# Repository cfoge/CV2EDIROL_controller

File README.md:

# CV2EDIROL_controller
An open-source CV to MIDI controller for EDIROL V4 and V8 video mixers

Programing guide: [link](https://docs.google.com/document/d/18BVAYo14xsvCTc38q8JL8ZcNEWuq-BcZkRPL7WG5LXM/edit?usp=sharing)

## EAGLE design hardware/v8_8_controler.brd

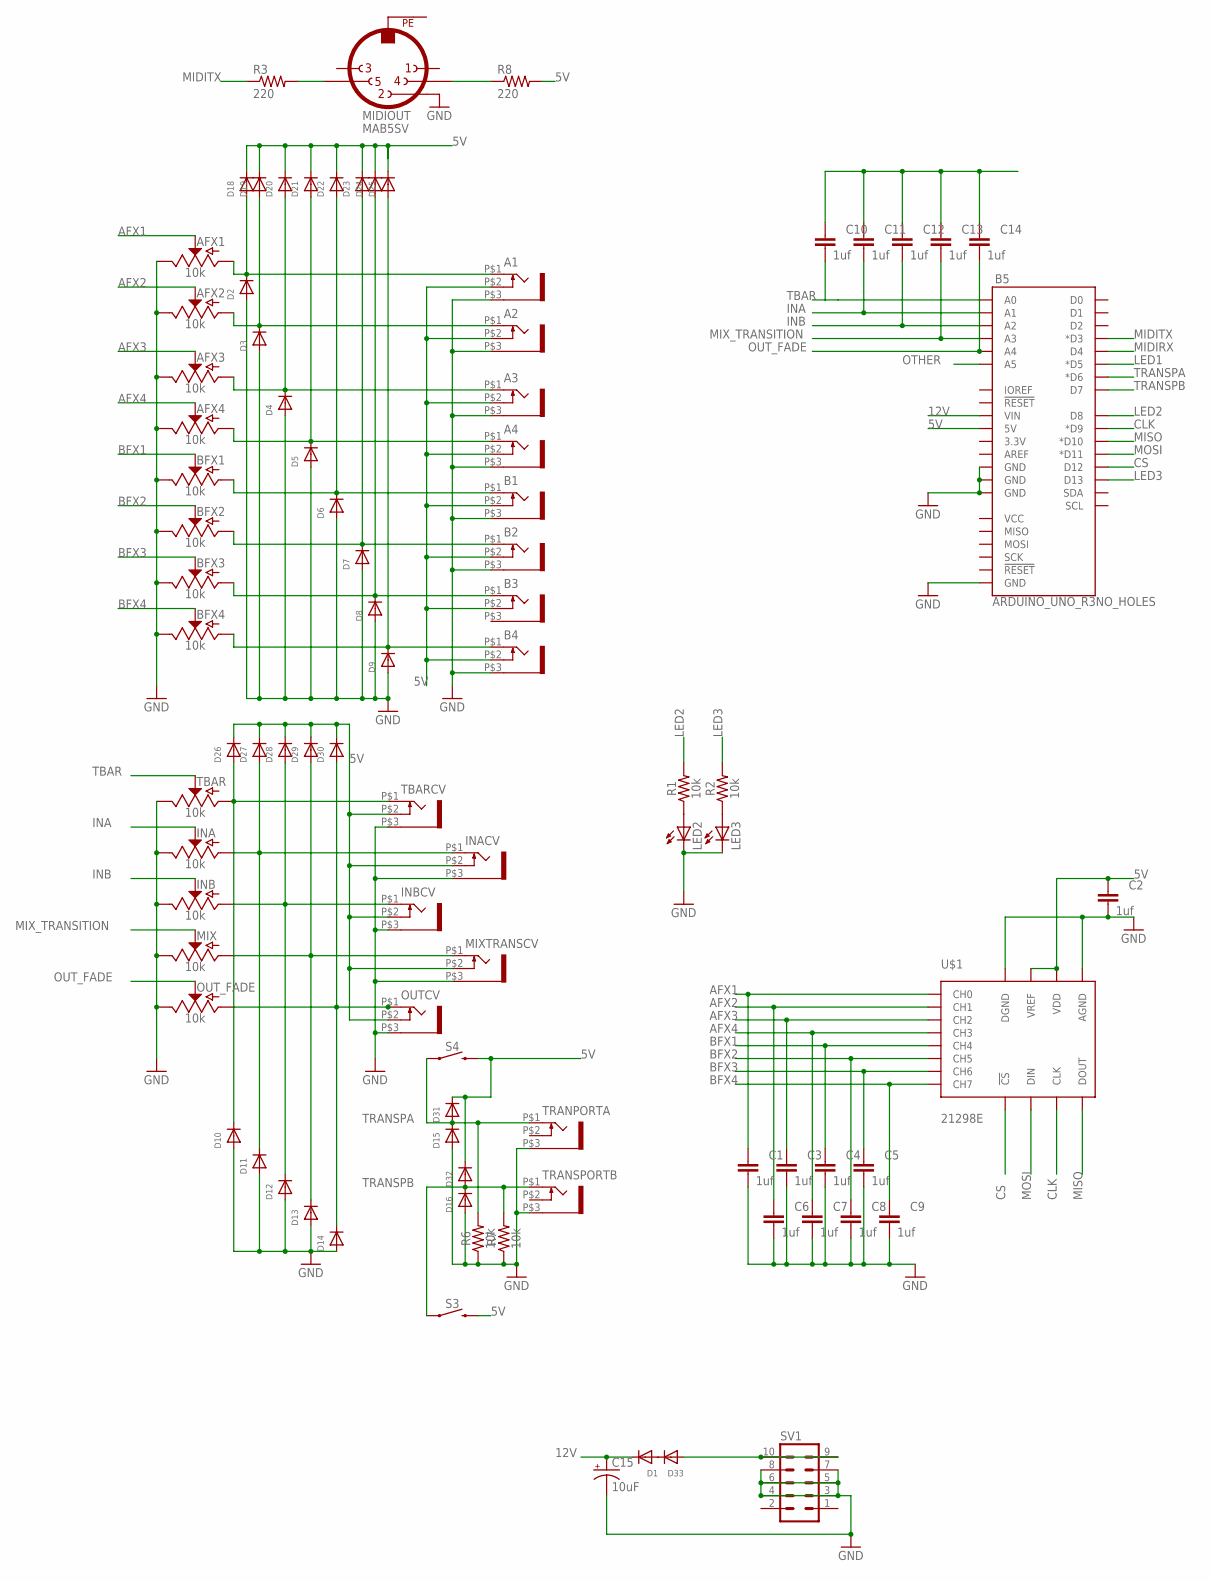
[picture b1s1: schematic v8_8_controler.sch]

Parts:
A1, A2, A3, A4: WQP-PJ301M-12_JACK
AFX1, AFX2, AFX3, AFX4: 10k; POT-PTH-ALPS
B1, B2, B3, B4: WQP-PJ301M-12_JACK
B5: ARDUINO_UNO_R3NO_HOLES; ARDUINO_R3_NO_HOLES
BFX1, BFX2, BFX3, BFX4: 10k; POT-PTH-ALPS
C1, C2, C3, C4, C5, C6, C7, C8, C9, C10, C11, C12, C13, C14: 1uf; 0805
C15: 10uF; EIA3528
D1, D2, D3, D4, D5, D6, D7, D8, D9, D10, D11, D12, D13, D14, D15, D16, D18, D19, D20, D21, D22, D23, D24, D25, D26, D27, D28, D29, D30, D31, D32, D33: DIODE_SOD-123FL; SOD-123FL
INA: 10k; POT-PTH-ALPS
INACV: WQP-PJ301M-12_JACK
INB: 10k; POT-PTH-ALPS
INBCV: WQP-PJ301M-12_JACK
LED2, LED3: LED3MM
MIDIOUT: MAB5SV
MIX: 10k; POT-PTH-ALPS
MIXTRANSCV: WQP-PJ301M-12_JACK
OUTCV: WQP-PJ301M-12_JACK
OUT_FADE: 10k; POT-PTH-ALPS
R1, R2, R6, R7: 10k; 0805
R3, R8: 220; R0805
S3, S4: MOMENTARY-SWITCH-SPST-PTH-6.0MM; TACTILE_SWITCH_PTH_6.0MM
SV1: MA05-2
TBAR: 10k; POT-PTH-ALPS
TBARCV: WQP-PJ301M-12_JACK
TRANPORTA: WQP-PJ301M-12_JACK
TRANSPORTB: WQP-PJ301M-12_JACK
U$1: 21298E; PDIP16

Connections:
5V: A1.P$2 (3), A2.P$2 (3), A3.P$2 (3), A4.P$2 (3), B1.P$2 (3), B2.P$2 (3), B3.P$2 (3), B4.P$2 (3), B5.5V, C2.1, D18.C, D19.C, D20.C, D21.C, D22.C, D23.C, D24.C, D25.C, D26.C, D27.C, D28.C, D29.C, D30.C, D31.C, D32.C, INACV.P$2 (3), INBCV.P$2 (3), MIXTRANSCV.P$2 (3), OUTCV.P$2 (3), R8.2, S3.3 (2), S4.3 (2), TBARCV.P$2 (3), U$1.P$15 (VREF), U$1.P$16 (VDD)
12V: B5.VIN, C15.A (+), D1.C
AFX1: AFX1.P$2 (S), C1.1, U$1.P$1 (CH0)
AFX2: AFX2.P$2 (S), C6.1, U$1.P$2 (CH1)
AFX3: AFX3.P$2 (S), C3.1, U$1.P$3 (CH2)
AFX4: AFX4.P$2 (S), C7.1, U$1.P$4 (CH3)
BFX1: BFX1.P$2 (S), C4.1, U$1.P$5 (CH4)
BFX2: BFX2.P$2 (S), C8.1, U$1.P$6 (CH5)
BFX3: BFX3.P$2 (S), C5.1, U$1.P$7 (CH6)
BFX4: BFX4.P$2 (S), C9.1, U$1.P$8 (CH7)
CLK: B5.D9 (*D9), U$1.P$13 (CLK)
CS: B5.D12, U$1.P$10 (!CS)
GND: A1.P$3 (1), A2.P$3 (1), A3.P$3 (1), A4.P$3 (1), AFX1.P$1 (E), AFX2.P$1 (E), AFX3.P$1 (E), AFX4.P$1 (E), B1.P$3 (1), B2.P$3 (1), B4.P$3 (1), B5.GND@1 (GND), B5.GND@2 (GND), B5.GND@3 (GND), B5.GND@4 (GND), BFX1.P$1 (E), BFX2.P$1 (E), BFX3.P$1 (E), BFX4.P$1 (E), C1.2, C2.2, C3.2, C4.2, C5.2, C6.2, C7.2, C8.2, C9.2, C15.C (-), D2.A, D3.A, D4.A, D5.A, D6.A, D7.A, D8.A, D9.A, D10.A, D11.A, D12.A, D13.A, D14.A, D15.A, D16.A, INA.P$1 (E), INACV.P$3 (1), INB.P$1 (E), INBCV.P$3 (1), LED2.K (C), LED3.K (C), MIDIOUT.2, MIX.P$1 (E), MIXTRANSCV.P$3 (1), OUTCV.P$3 (1), OUT_FADE.P$1 (E), R6.1, R7.1, SV1.3, SV1.4, SV1.5, SV1.6, SV1.7, SV1.8, TBAR.P$1 (E), TBARCV.P$3 (1), TRANPORTA.P$3 (1), TRANSPORTB.P$3 (1), U$1.P$9 (DGND), U$1.P$14 (AGND)
INA: B5.A1, C11.2, INA.P$2 (S)
INB: B5.A2, C12.2, INB.P$2 (S)
LED1: B5.D5 (*D5)
LED2: B5.D8, R1.2
LED3: B5.D13, R2.2
MIDIRX: B5.D4
MIDITX: B5.D3 (*D3), R3.1
MISO: B5.D10 (*D10), U$1.P$12 (DOUT)
MIX_TRANSITION: B5.A3, C13.2, MIX.P$2 (S)
MOSI: B5.D11 (*D11), U$1.P$11 (DIN)
unnamed: A1.P$1 (2), AFX1.P$3 (A), D2.C, D18.A
unnamed: A2.P$1 (2), AFX2.P$3 (A), D3.C, D19.A
unnamed: A3.P$1 (2), AFX3.P$3 (A), D4.C, D20.A
unnamed: A4.P$1 (2), AFX4.P$3 (A), D5.C, D21.A
unnamed: B1.P$1 (2), BFX1.P$3 (A), D6.C, D22.A
unnamed: B2.P$1 (2), BFX2.P$3 (A), D7.C, D23.A
unnamed: B3.P$1 (2), BFX3.P$3 (A), D8.C, D24.A
unnamed: B4.P$1 (2), BFX4.P$3 (A), D9.C, D25.A
unnamed: MIDIOUT.4, R8.1
unnamed: LED2.A, R1.1
unnamed: MIDIOUT.5, R3.2
unnamed: LED3.A, R2.1
unnamed: D1.A, D33.C
unnamed: D10.C, D26.A, TBAR.P$3 (A), TBARCV.P$1 (2)
unnamed: D11.C, D27.A, INA.P$3 (A), INACV.P$1 (2)
unnamed: D12.C, D28.A, INB.P$3 (A), INBCV.P$1 (2)
unnamed: D13.C, D29.A, MIX.P$3 (A), MIXTRANSCV.P$1 (2)
unnamed: D14.C, D30.A, OUTCV.P$1 (2), OUT_FADE.P$3 (A)
unnamed: C10.1, C11.1, C12.1, C13.1, C14.1
unnamed: D33.A, SV1.9, SV1.10
OTHER: B5.A5
OUT_FADE: B5.A4, C14.2, OUT_FADE.P$2 (S)
PE: MIDIOUT.PE
TBAR: B5.A0, C10.2, TBAR.P$2 (S)
TRANSPA: B5.D6 (*D6), D15.C, D31.A, R6.2, S4.1, TRANPORTA.P$1 (2)
TRANSPB: B5.D7, D16.C, D32.A, R7.2, S3.1, TRANSPORTB.P$1 (2)

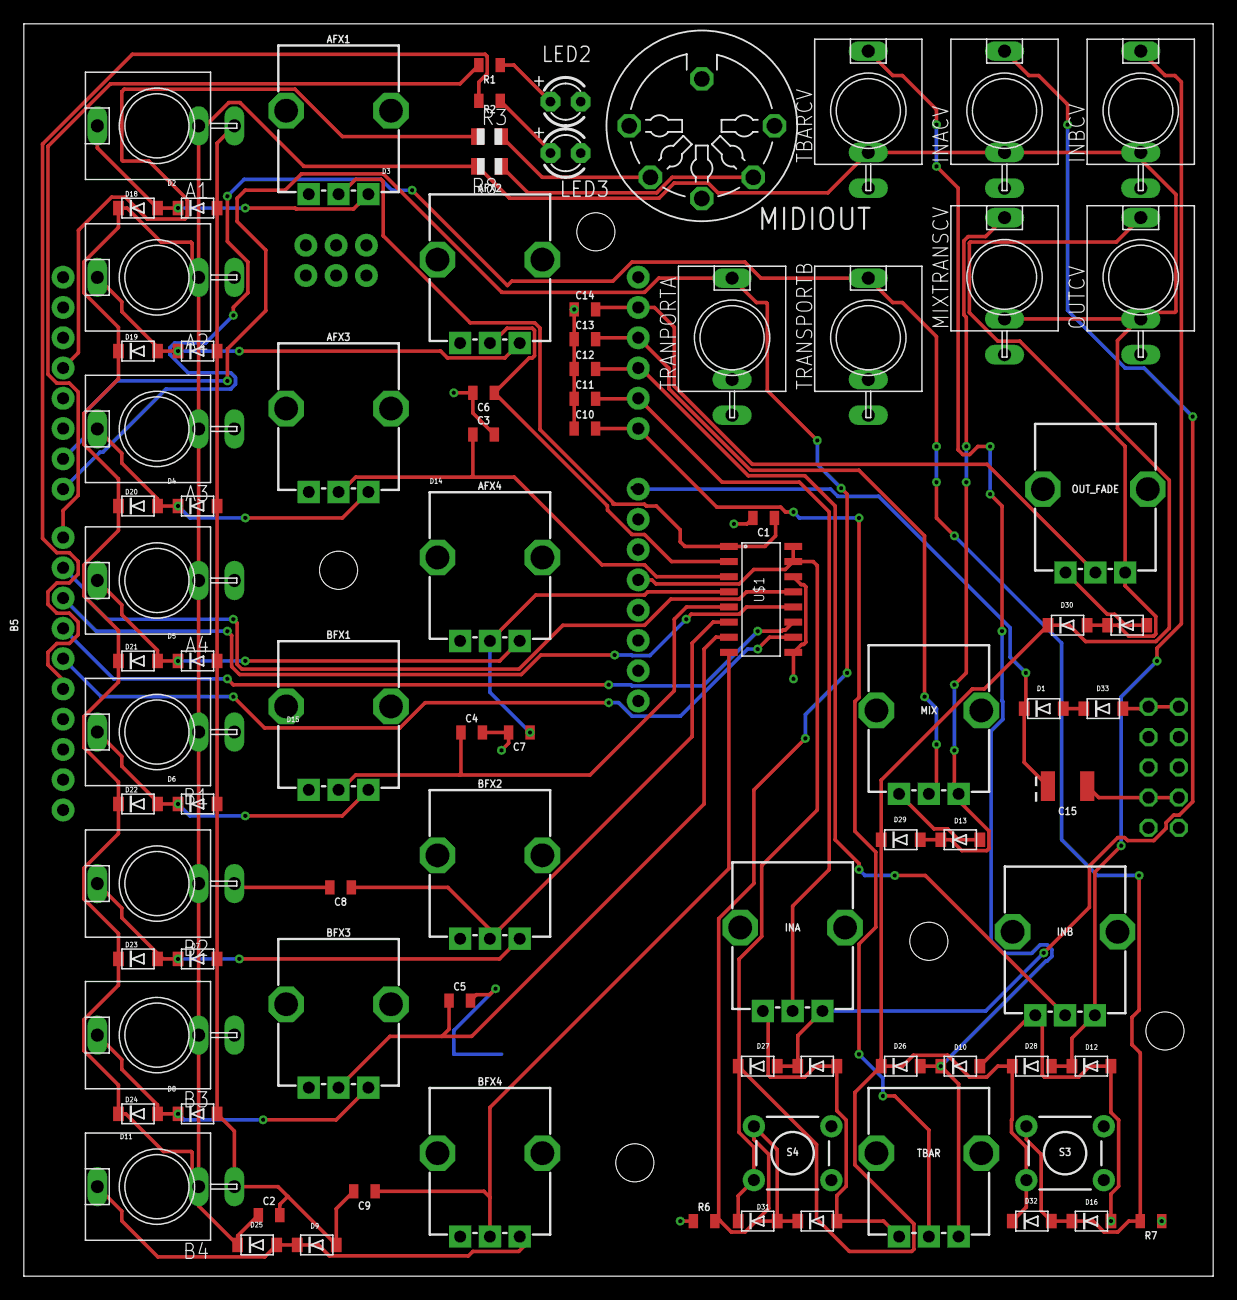
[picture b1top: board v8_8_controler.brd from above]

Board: 2 copper layers, 99.8 x 105.1 mm, 89 parts (1 on the bottom side), 45 nets.

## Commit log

2021-08-31 Add files via upload
    better spacing and test front pannel
2021-12-04 latest code file

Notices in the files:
parts and their libraries:
SparkFun-Resistors: Licensing: Creative Commons ShareAlike 4.0 International - https://creativecommons.org/licenses/by-sa/4.0
